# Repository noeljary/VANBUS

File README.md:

# VANBUS
Circuits and MCU Code for Camper Van Electronics Control Systems

VANBUS will be a series of circuit boards designed to control all electronic systems within a camper van conversion. It is based on a CANBUS network for inter-board communiciations.

This repository contains the Autodesk EAGLE files for the circuit boards, links to the custom designed cases, and the microcontroller code used to control the system.

Boards:
- LIGHTING_CTL_BOARD: Circuit Board for PWM Control of LED Lighting
- MOSFET_CTL_BOARD: Circuit Board for Fused Power Distribution with Voltage/Current per Channel Monitoring
- REMOTE_SWITCH_BOARD: Circuit Board for Remote Switching of MOSFET/Lighting Circuits with Momentary/Latched Switching, and Status Indication
- CAPACITIVE_SWITCH_BOARD: Circuit Board for Dimming Control of Lighting Circuits with Capacitive Touch Slider
- MOSFET_POC: Proof of Concept Circuit Board for MOSET based solid state relay system
- VANBUS_HUB: Circuit Board for Central Connection of CANBUS connectors where daisy chaining is not possible

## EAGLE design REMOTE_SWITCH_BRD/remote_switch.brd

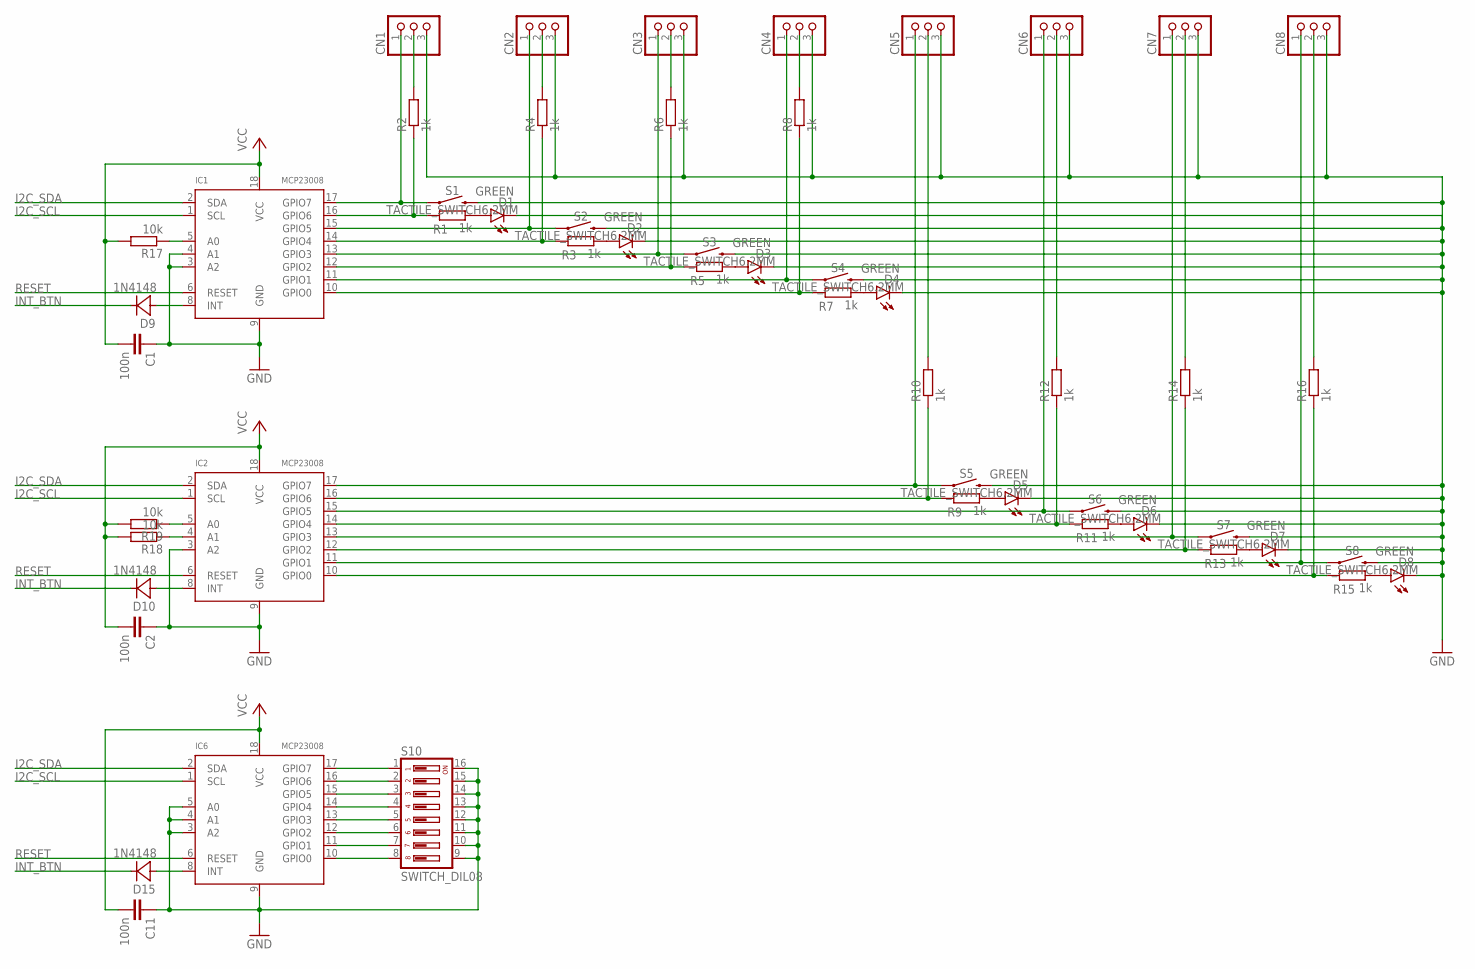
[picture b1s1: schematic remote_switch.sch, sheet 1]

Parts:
C1, C2, C11: 100n; C0805
CN1, CN2, CN3, CN4, CN5, CN6, CN7, CN8: JST_3PIN; JSTPH3
D1, D2, D3, D4, D5, D6, D7, D8: GREEN; CHIPLED_1206
D9, D10, D15: 1N4148; SOD123
IC1, IC2, IC6: MCP23008; SO18W
R1, R2, R3, R4, R5, R6, R7, R8, R9, R10, R11, R12, R13, R14, R15, R16: 1k; R0805
R17, R18, R19: 10k; R0805
S1, S2, S3, S4, S5, S6, S7, S8: TACTILE_SWITCH6.2MM; TACTILE_SWITCH_SMD_6.2MM
S10: SWITCH_DIL08; CTS-219-08

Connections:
GND: C1.1, C2.1, C11.1, CN1.3, CN2.3, CN3.3, CN4.3, CN5.3, CN6.3, CN7.3, CN8.3, D1.C, D2.C, D3.C, D4.C, D5.C, D6.C, D7.C, D8.C, IC1.3 (A2), IC1.4 (A1), IC1.9 (GND), IC2.3 (A2), IC2.9 (GND), IC6.3 (A2), IC6.4 (A1), IC6.5 (A0), IC6.9 (GND), S1.B1 (2), S1.B2 (2), S2.B1 (2), S2.B2 (2), S3.B1 (2), S3.B2 (2), S4.B1 (2), S4.B2 (2), S5.B1 (2), S5.B2 (2), S6.B1 (2), S6.B2 (2), S7.B1 (2), S7.B2 (2), S8.B1 (2), S8.B2 (2), S10.9, S10.10, S10.11, S10.12, S10.13, S10.14, S10.15, S10.16; also elsewhere on the board
I2C_SCL: IC1.1 (SCL), IC2.1 (SCL), IC6.1 (SCL); also elsewhere on the board
I2C_SDA: IC1.2 (SDA), IC2.2 (SDA), IC6.2 (SDA); also elsewhere on the board
INT_BTN: D9.C, D10.C, D15.C; also elsewhere on the board
unnamed: IC1.5 (A0), R17.1
unnamed: IC2.5 (A0), R19.1
unnamed: IC2.4 (A1), R18.1
unnamed: IC6.17 (GPIO7), S10.1
unnamed: IC6.16 (GPIO6), S10.2
unnamed: IC6.15 (GPIO5), S10.3
unnamed: IC6.14 (GPIO4), S10.4
unnamed: IC6.13 (GPIO3), S10.5
unnamed: IC6.12 (GPIO2), S10.6
unnamed: IC6.11 (GPIO1), S10.7
unnamed: CN1.1, IC1.17 (GPIO7), S1.A1 (1), S1.A2 (1)
unnamed: CN2.1, IC1.15 (GPIO5), S2.A1 (1), S2.A2 (1)
unnamed: CN3.1, IC1.13 (GPIO3), S3.A1 (1), S3.A2 (1)
unnamed: CN4.1, IC1.11 (GPIO1), S4.A1 (1), S4.A2 (1)
unnamed: CN5.1, IC2.17 (GPIO7), S5.A1 (1), S5.A2 (1)
unnamed: CN6.1, IC2.15 (GPIO5), S6.A1 (1), S6.A2 (1)
unnamed: CN7.1, IC2.13 (GPIO3), S7.A1 (1), S7.A2 (1)
unnamed: CN8.1, IC2.11 (GPIO1), S8.A1 (1), S8.A2 (1)
unnamed: D1.A, R1.2
unnamed: D2.A, R3.2
unnamed: D3.A, R5.2
unnamed: D4.A, R7.2
unnamed: D5.A, R9.2
unnamed: D6.A, R11.2
unnamed: D7.A, R13.2
unnamed: D8.A, R15.2
unnamed: CN1.2, R2.2
unnamed: IC1.16 (GPIO6), R1.1, R2.1
unnamed: CN2.2, R4.2
unnamed: CN3.2, R6.2
unnamed: CN4.2, R8.2
unnamed: CN5.2, R10.2
unnamed: CN6.2, R12.2
unnamed: CN7.2, R14.2
unnamed: CN8.2, R16.2
unnamed: IC1.14 (GPIO4), R3.1, R4.1
unnamed: IC1.12 (GPIO2), R5.1, R6.1
unnamed: IC1.10 (GPIO0), R7.1, R8.1
unnamed: IC2.16 (GPIO6), R9.1, R10.1
unnamed: IC2.14 (GPIO4), R11.1, R12.1
unnamed: IC2.12 (GPIO2), R13.1, R14.1
unnamed: IC2.10 (GPIO0), R15.1, R16.1
unnamed: IC6.10 (GPIO0), S10.8
unnamed: D10.A, IC2.8 (INT)
unnamed: D9.A, IC1.8 (INT)
unnamed: D15.A, IC6.8 (INT)
RESET: IC1.6 (RESET), IC2.6 (RESET), IC6.6 (RESET); also elsewhere on the board
VCC: C1.2, C2.2, C11.2, IC1.18 (VCC), IC2.18 (VCC), IC6.18 (VCC), R17.2, R18.2, R19.2; also elsewhere on the board

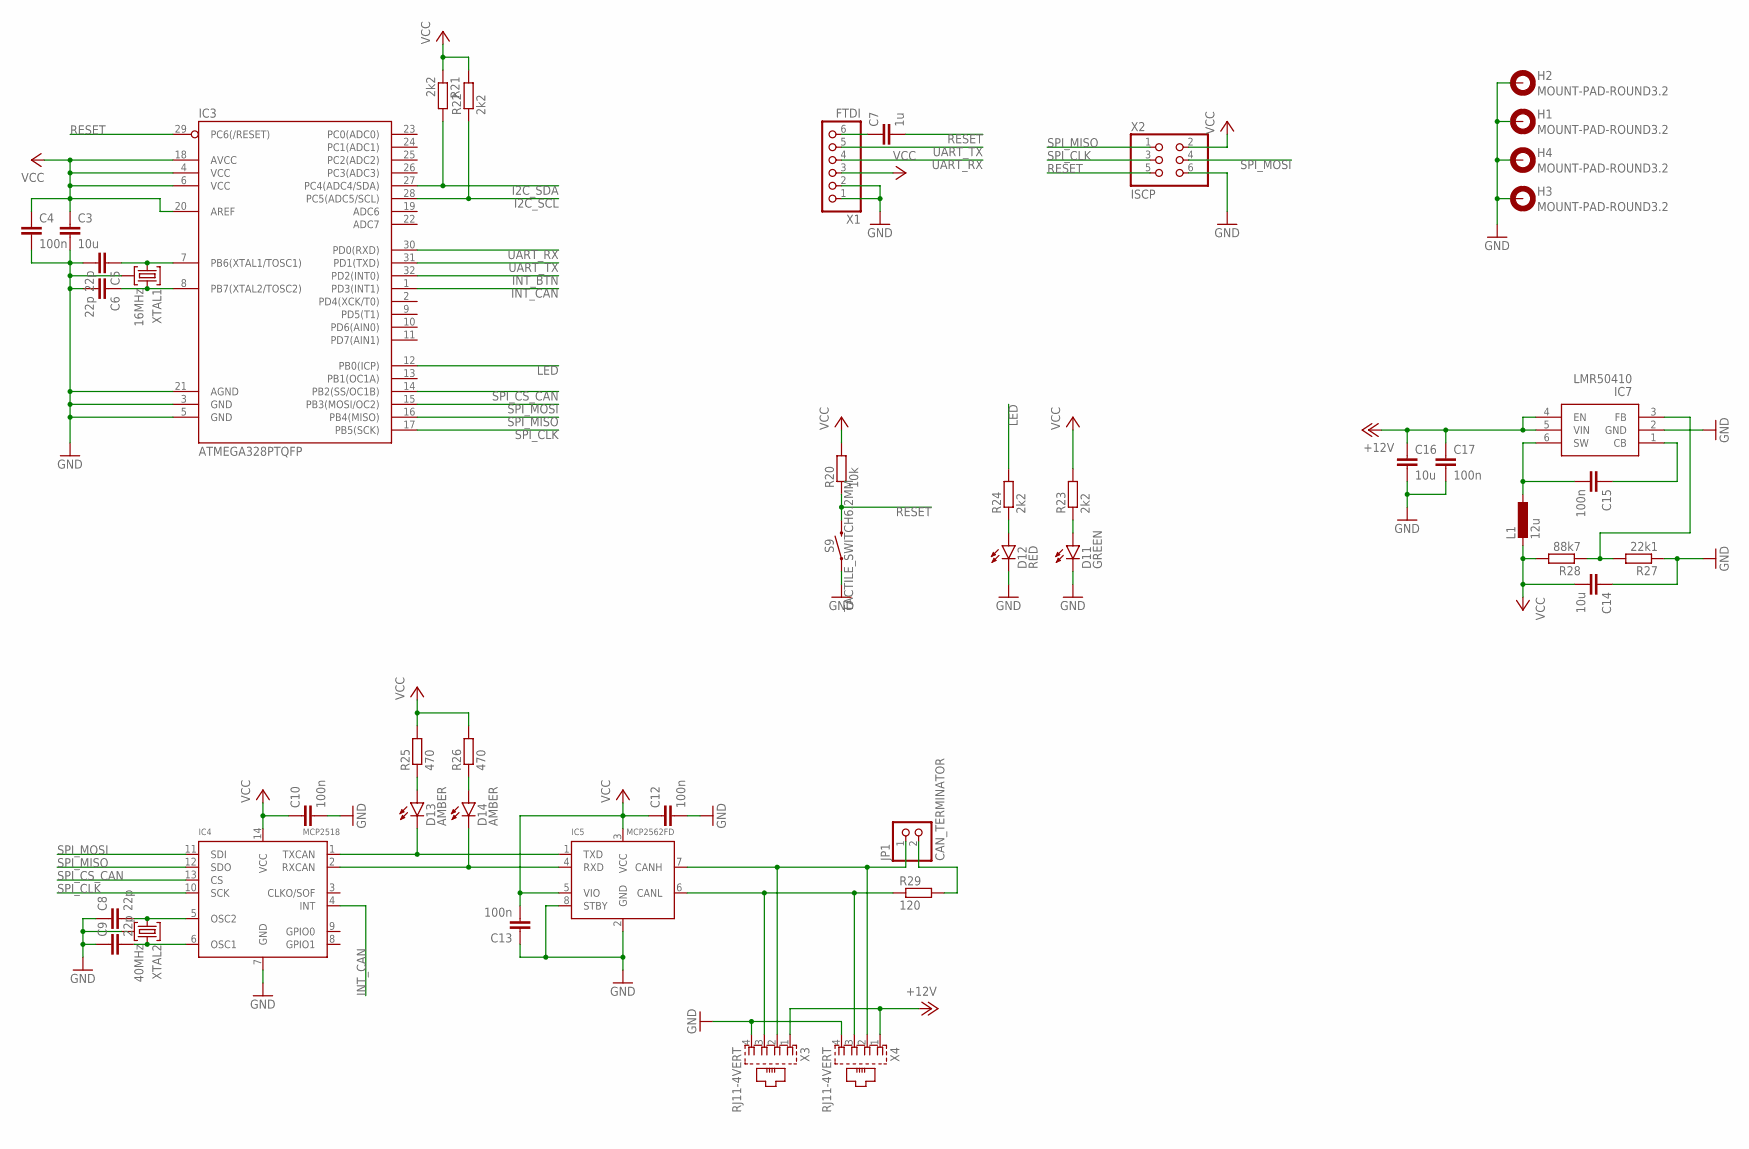
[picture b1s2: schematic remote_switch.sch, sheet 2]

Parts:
C3, C14, C16: 10u; C1206
C4, C10, C12, C13, C15, C17: 100n; C0805
C5, C6, C8, C9: 22p; C0805
C7: 1u; C0805
D11: GREEN; CHIPLED_1206
D12: RED; CHIPLED_1206
D13, D14: AMBER; CHIPLED_1206
H1, H2, H3, H4: MOUNT-PAD-ROUND3.2; 3,2-PAD
IC3: ATMEGA328PTQFP; TQFP32_0.8MM_7X7MM
IC4: MCP2518; SO14
IC5: MCP2562FD; SO08
IC7: LMR50410; SOT23-6
JP1: CAN_TERMINATOR; 1X02
L1: 12u; L_7.3MM
R20: 10k; R0805
R21, R22, R23, R24: 2k2; R0805
R25, R26: 470; R0805
R27: 22k1; R0805
R28: 88k7; R0805
R29: 120; R0805
S9: TACTILE_SWITCH6.2MM; TACTILE_SWITCH_SMD_6.2MM
X1: FTDI; 1X06
X2: ISCP; 2X03
X3, X4: RJ11-4VERT; RJ11-4_VERT
XTAL1: 16MHz; XTAL_5.0X3.2_4
XTAL2: 40MHz; XTAL_5.0X3.2_4

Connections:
+12V: C16.1, C17.1, IC7.4 (EN), IC7.5 (VIN), X3.1, X4.1
GND: C3.2, C4.2, C5.2, C6.2, C8.1, C9.1, C10.2, C12.2, C13.1, C14.1, C16.2, C17.2, D11.C, D12.C, H1.B3,2, H1.P$1, H1.P$2, H1.P$3, H1.P$4, H1.P$5, H1.P$6, H1.P$7, H1.P$8, H2.B3,2, H2.P$1, H2.P$2, H2.P$3, H2.P$4, H2.P$5, H2.P$6, H2.P$7, H2.P$8, H3.B3,2, H3.P$1, H3.P$2, H3.P$3, H3.P$4, H3.P$5, H3.P$6, H3.P$7, H3.P$8, H4.B3,2, H4.P$1, H4.P$2, H4.P$3, H4.P$4, H4.P$5, H4.P$6, H4.P$7, H4.P$8, IC3.3 (GND), IC3.5 (GND), IC3.21 (AGND), IC4.7 (GND), IC5.2 (GND), IC5.8 (STBY), IC7.2 (GND), R27.1, S9.A1 (1), S9.A2 (1), X1.1, X1.2, X2.6, X3.4, X4.4, XTAL1.2, XTAL1.4 (2), XTAL2.2, XTAL2.4 (2); also elsewhere on the board
I2C_SCL: IC3.28 (PC5(ADC5/SCL)), R22.1; also elsewhere on the board
I2C_SDA: IC3.27 (PC4(ADC4/SDA)), R21.2; also elsewhere on the board
INT_BTN: IC3.32 (PD2(INT0)); also elsewhere on the board
INT_CAN: IC3.1 (PD3(INT1)), IC4.4 (INT)
LED: IC3.12 (PB0(ICP)), R24.2
unnamed: D12.A, R24.1
unnamed: C5.1, IC3.7 (PB6(XTAL1/TOSC1)), XTAL1.1
unnamed: C6.1, IC3.8 (PB7(XTAL2/TOSC2)), XTAL1.3
unnamed: D11.A, R23.1
unnamed: C7.1, X1.6
unnamed: IC5.6 (CANL), R29.1, X3.3, X4.3
unnamed: IC5.7 (CANH), JP1.1, X3.2, X4.2
unnamed: D13.C, IC4.1 (TXCAN), IC5.1 (TXD)
unnamed: D14.C, IC4.2 (RXCAN), IC5.4 (RXD)
unnamed: C8.2, IC4.5 (OSC2), XTAL2.1
unnamed: C9.2, IC4.6 (OSC1), XTAL2.3
unnamed: D13.A, R25.1
unnamed: D14.A, R26.1
unnamed: JP1.2, R29.2
unnamed: C15.2, IC7.6 (SW), L1.1
unnamed: C15.1, IC7.1 (CB)
unnamed: IC7.3 (FB), R27.2, R28.1
RESET: C7.2, IC3.29 (PC6(/RESET)), R20.1, S9.B1 (2), S9.B2 (2), X2.5; also elsewhere on the board
SPI_CLK: IC3.17 (PB5(SCK)), IC4.10 (SCK), X2.3
SPI_CS_CAN: IC3.14 (PB2(SS/OC1B)), IC4.13 (CS)
SPI_MISO: IC3.16 (PB4(MISO)), IC4.12 (SDO), X2.1
SPI_MOSI: IC3.15 (PB3(MOSI/OC2)), IC4.11 (SDI), X2.4
UART_RX: IC3.30 (PD0(RXD)), X1.4
UART_TX: IC3.31 (PD1(TXD)), X1.5
VCC: C3.1, C4.1, C10.1, C12.1, C13.2, C14.2, IC3.4 (VCC), IC3.6 (VCC), IC3.18 (AVCC), IC3.20 (AREF), IC4.14 (VCC), IC5.3 (VCC), IC5.5 (VIO), L1.2, R20.2, R21.1, R22.2, R23.2, R25.2, R26.2, R28.2, X1.3, X2.2; also elsewhere on the board

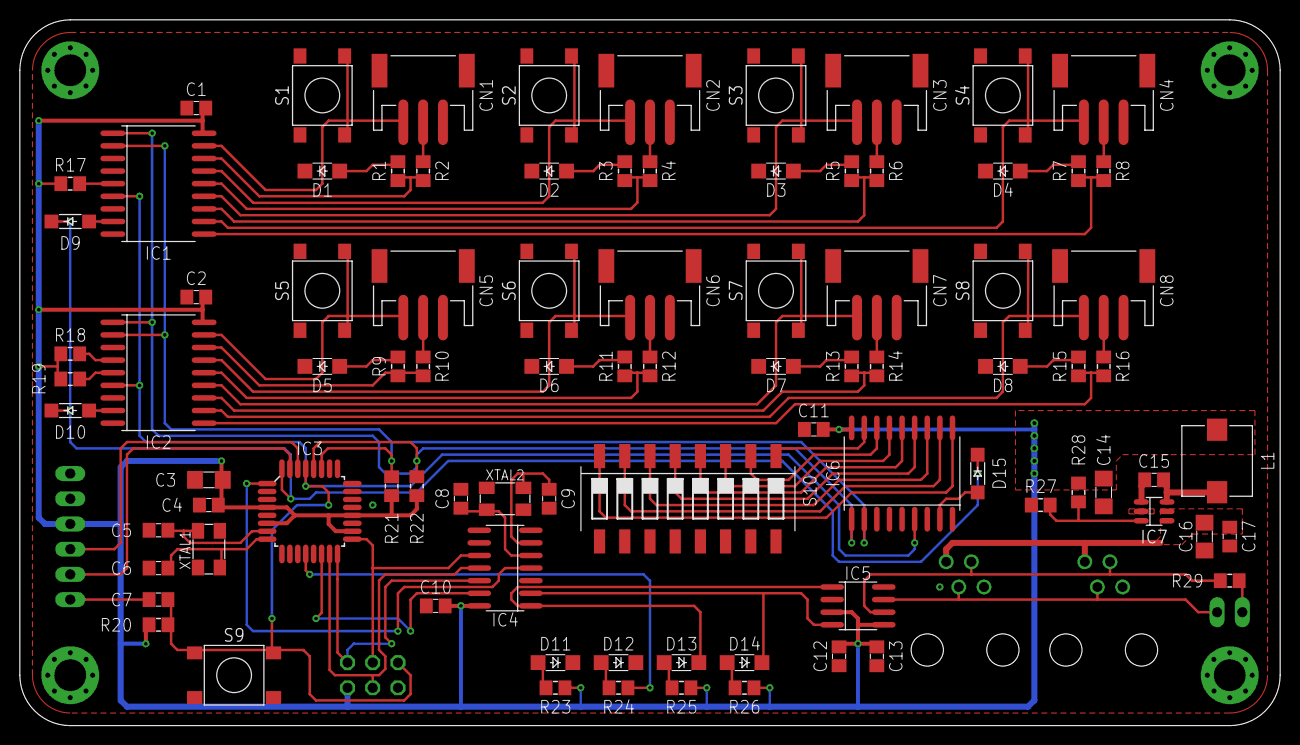
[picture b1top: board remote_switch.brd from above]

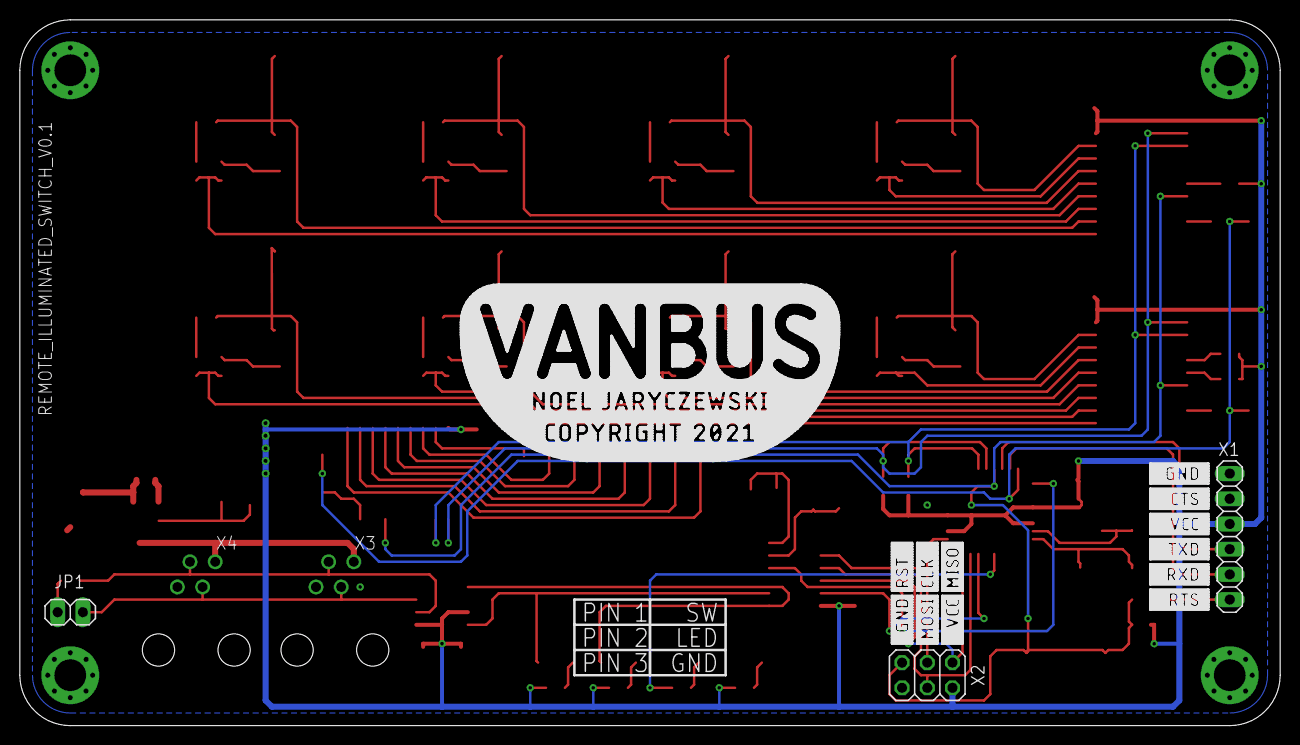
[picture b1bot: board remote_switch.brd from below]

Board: 2 copper layers, 127.0 x 71.1 mm, 98 parts (5 on the bottom side), 78 nets.

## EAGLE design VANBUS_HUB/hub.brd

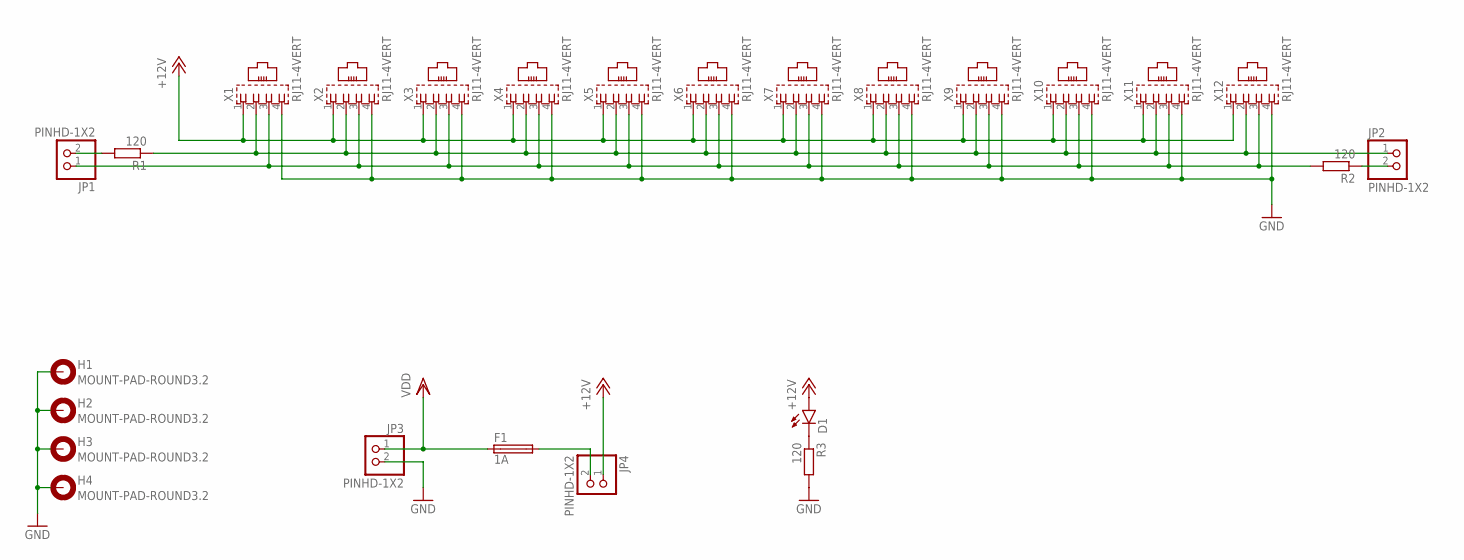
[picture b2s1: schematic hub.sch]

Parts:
D1: LED1206; CHIPLED_1206
F1: 1A; 5X20_FUSE
H1, H2, H3, H4: MOUNT-PAD-ROUND3.2; 3,2-PAD
JP1, JP2, JP3, JP4: PINHD-1X2; 1X02
R1, R2, R3: 120; R0805
X1, X2, X3, X4, X5, X6, X7, X8, X9, X10, X11, X12: RJ11-4VERT; RJ11-4_VERT

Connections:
+12V: D1.A, JP4.1, X1.1, X2.1, X3.1, X4.1, X5.1, X6.1, X7.1, X8.1, X9.1, X10.1, X11.1, X12.1
GND: H1.B3,2, H1.P$1, H1.P$2, H1.P$3, H1.P$4, H1.P$5, H1.P$6, H1.P$7, H1.P$8, H2.B3,2, H2.P$1, H2.P$2, H2.P$3, H2.P$4, H2.P$5, H2.P$6, H2.P$7, H2.P$8, H3.B3,2, H3.P$1, H3.P$2, H3.P$3, H3.P$4, H3.P$5, H3.P$6, H3.P$7, H3.P$8, H4.B3,2, H4.P$1, H4.P$2, H4.P$3, H4.P$4, H4.P$5, H4.P$6, H4.P$7, H4.P$8, JP3.2, R3.2, X1.4, X2.4, X3.4, X4.4, X5.4, X6.4, X7.4, X8.4, X9.4, X10.4, X11.4, X12.4
unnamed: JP2.2, R2.1
unnamed: JP2.1, R1.1, X1.2, X2.2, X3.2, X4.2, X5.2, X6.2, X7.2, X8.2, X9.2, X10.2, X11.2, X12.2
unnamed: JP1.1, R2.2, X1.3, X2.3, X3.3, X4.3, X5.3, X6.3, X7.3, X8.3, X9.3, X10.3, X11.3, X12.3
unnamed: JP1.2, R1.2
unnamed: D1.C, R3.1
unnamed: F1.2A (2), F1.2B (2), JP4.2
VDD: F1.1A (1), F1.1B (1), JP3.1

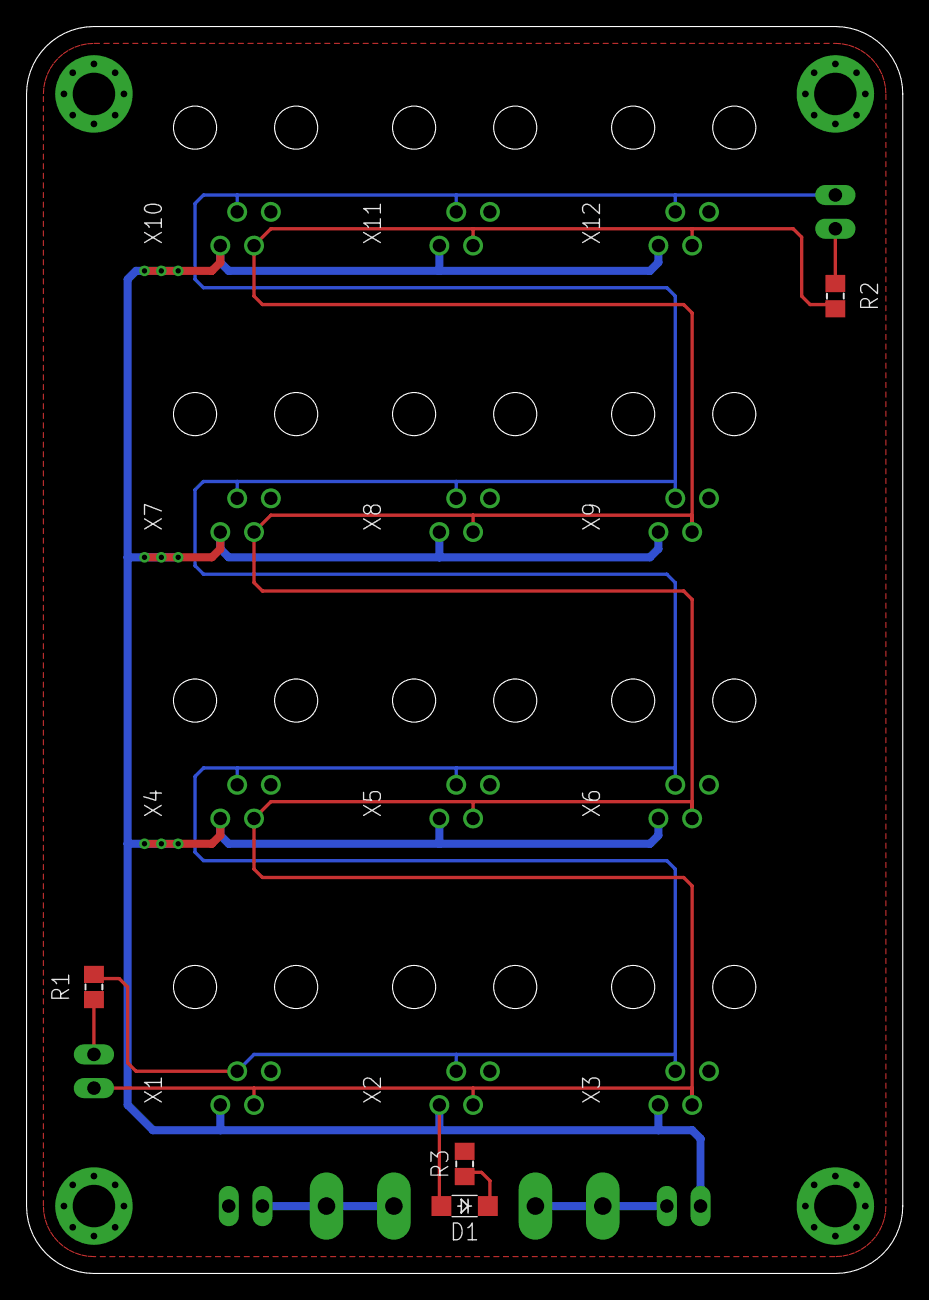
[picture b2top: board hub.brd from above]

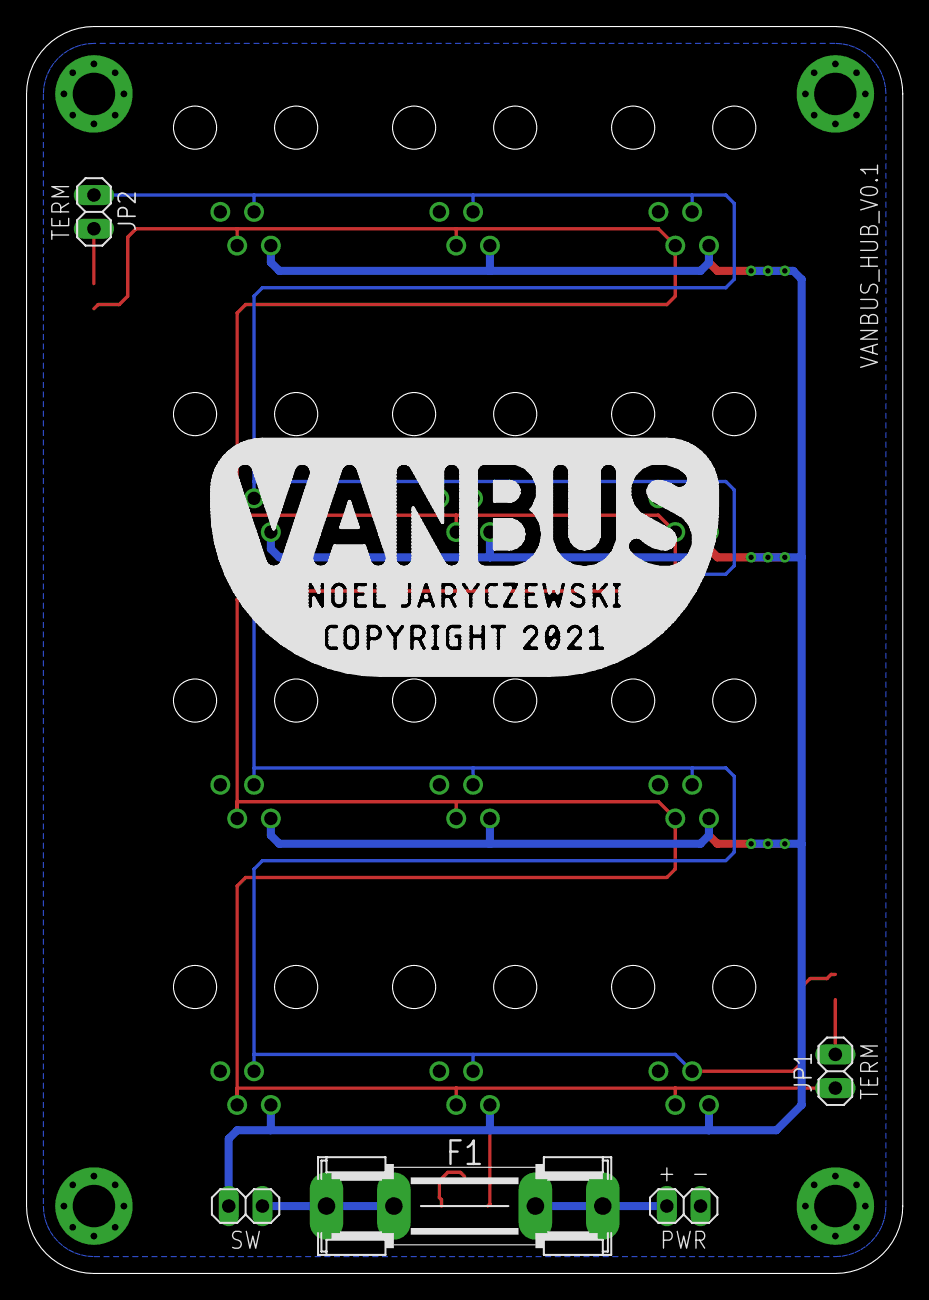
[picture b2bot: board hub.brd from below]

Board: 2 copper layers, 66.0 x 94.0 mm, 25 parts (5 on the bottom side), 9 nets.

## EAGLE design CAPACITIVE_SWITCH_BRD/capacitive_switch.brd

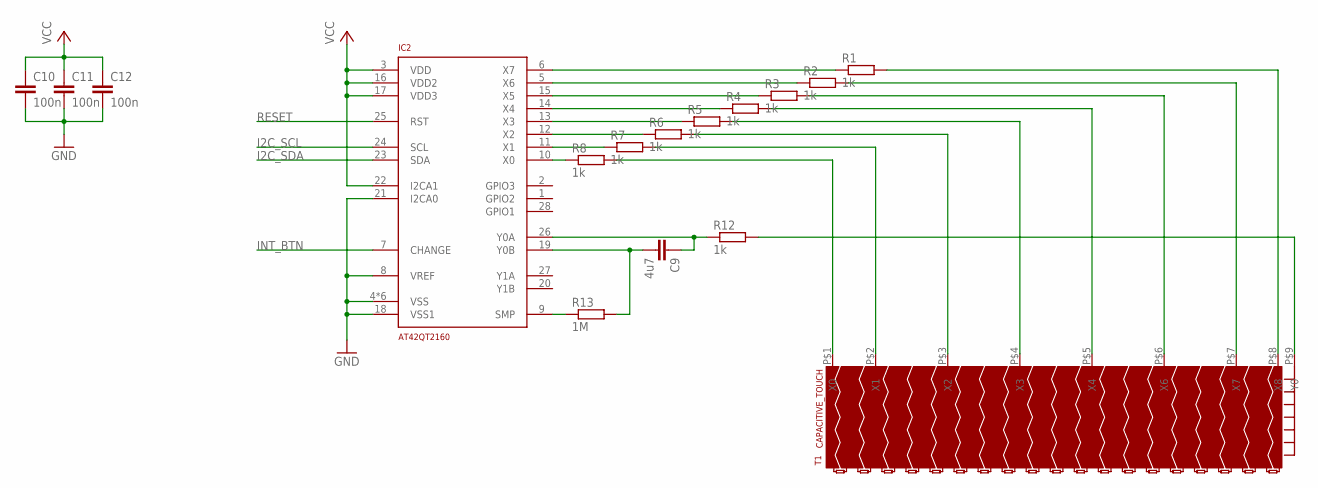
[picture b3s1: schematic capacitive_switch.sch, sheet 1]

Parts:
C9: 4u7; C0805
C10, C11, C12: 100n; C0805
IC2: AT42QT2160; QFN28_0.45MM_4X4MM
R1, R2, R3, R4, R5, R6, R7, R8, R12: 1k; R0805
R13: 1M; R0805
T1: CAPACITIVE_TOUCH; 90X20_CAPACITIVE_TOUCH

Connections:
GND: C10.2, C11.2, C12.2, IC2.4 (VSS), IC2.8 (VREF), IC2.18 (VSS1), IC2.21 (I2CA0), IC2.29 (VSS), IC2.P$1 (VSS), IC2.P$2 (VSS), IC2.P$3 (VSS), IC2.P$4 (VSS); also elsewhere on the board
I2C_SCL: IC2.24 (SCL); also elsewhere on the board
I2C_SDA: IC2.23 (SDA); also elsewhere on the board
INT_BTN: IC2.7 (CHANGE); also elsewhere on the board
unnamed: R8.2, T1.P$1 (X0)
unnamed: R7.2, T1.P$2 (X1)
unnamed: R6.2, T1.P$3 (X2)
unnamed: R5.2, T1.P$4 (X3)
unnamed: R4.2, T1.P$5 (X4)
unnamed: R3.2, T1.P$6 (X6)
unnamed: R2.2, T1.P$7 (X7)
unnamed: R1.2, T1.P$8 (X8)
unnamed: R12.2, T1.P$9 (Y0)
unnamed: C9.1, IC2.26 (Y0A), R12.1
unnamed: IC2.10 (X0), R8.1
unnamed: IC2.11 (X1), R7.1
unnamed: IC2.12 (X2), R6.1
unnamed: IC2.13 (X3), R5.1
unnamed: IC2.14 (X4), R4.1
unnamed: IC2.15 (X5), R3.1
unnamed: IC2.5 (X6), R2.1
unnamed: IC2.6 (X7), R1.1
unnamed: C9.2, IC2.19 (Y0B), R13.2
unnamed: IC2.9 (SMP), R13.1
RESET: IC2.25 (RST); also elsewhere on the board
VCC: C10.1, C11.1, C12.1, IC2.3 (VDD), IC2.16 (VDD2), IC2.17 (VDD3), IC2.22 (I2CA1); also elsewhere on the board

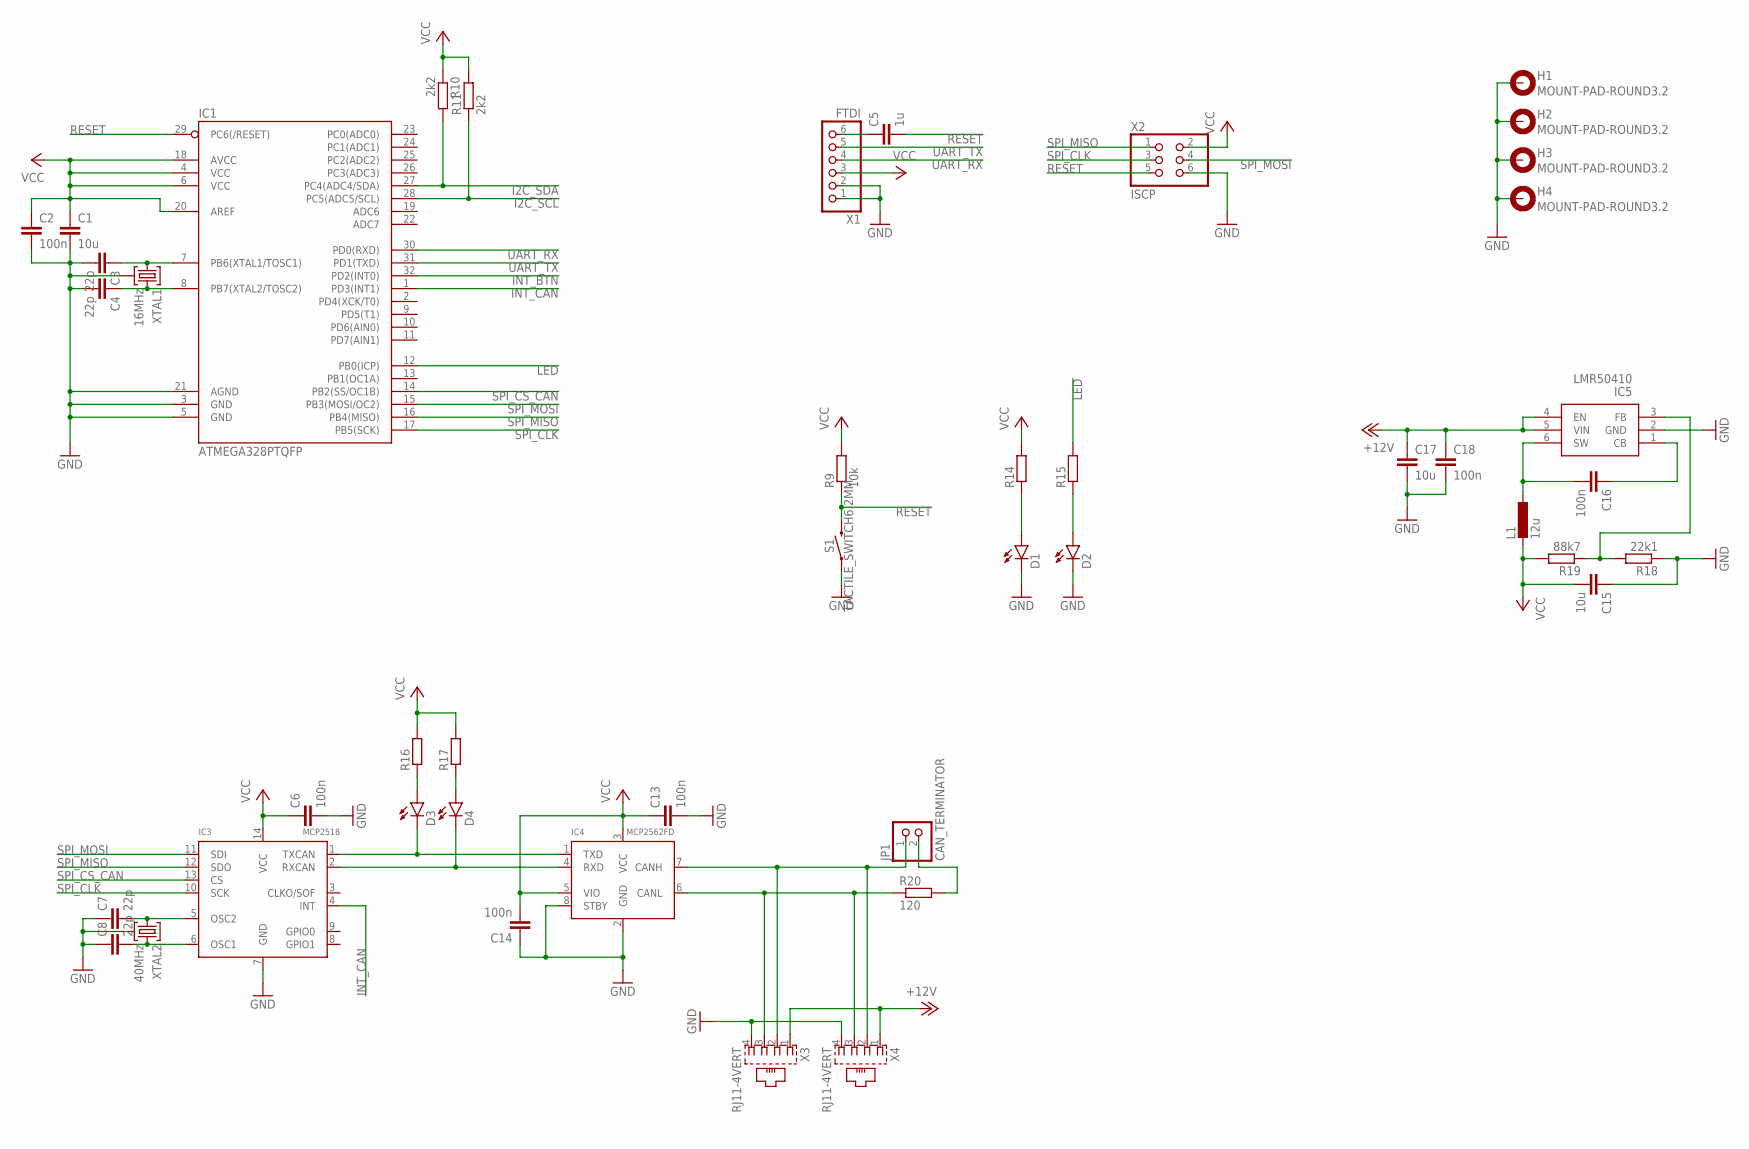
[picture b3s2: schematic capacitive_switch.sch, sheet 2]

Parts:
C1, C15, C17: 10u; C1206
C2, C6, C13, C14, C16, C18: 100n; C0805
C3, C4, C7, C8: 22p; C0805
C5: 1u; C0805
D1, D2, D3, D4: LED1206; CHIPLED_1206
H1, H2, H3, H4: MOUNT-PAD-ROUND3.2; 3,2-PAD
IC1: ATMEGA328PTQFP; TQFP32_0.8MM_7X7MM
IC3: MCP2518; SO14
IC4: MCP2562FD; SO08
IC5: LMR50410; SOT23-6
JP1: CAN_TERMINATOR; 1X02
L1: 12u; L_7.3MM
R9: 10k; R0805
R10, R11: 2k2; R0805
R14, R15, R16, R17: RESISTOR0805; R0805
R18: 22k1; R0805
R19: 88k7; R0805
R20: 120; R0805
S1: TACTILE_SWITCH6.2MM; TACTILE_SWITCH_SMD_6.2MM
X1: FTDI; 1X06
X2: ISCP; 2X03
X3, X4: RJ11-4VERT; RJ11-4_VERT
XTAL1: 16MHz; XTAL_5.0X3.2_4
XTAL2: 40MHz; XTAL_5.0X3.2_4

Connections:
+12V: C17.1, C18.1, IC5.4 (EN), IC5.5 (VIN), X3.1, X4.1
GND: C1.2, C2.2, C3.2, C4.2, C6.2, C7.1, C8.1, C13.2, C14.1, C15.1, C17.2, C18.2, D1.C, D2.C, H1.B3,2, H1.P$1, H1.P$2, H1.P$3, H1.P$4, H1.P$5, H1.P$6, H1.P$7, H1.P$8, H2.B3,2, H2.P$1, H2.P$2, H2.P$3, H2.P$4, H2.P$5, H2.P$6, H2.P$7, H2.P$8, H3.B3,2, H3.P$1, H3.P$2, H3.P$3, H3.P$4, H3.P$5, H3.P$6, H3.P$7, H3.P$8, H4.B3,2, H4.P$1, H4.P$2, H4.P$3, H4.P$4, H4.P$5, H4.P$6, H4.P$7, H4.P$8, IC1.3 (GND), IC1.5 (GND), IC1.21 (AGND), IC3.7 (GND), IC4.2 (GND), IC4.8 (STBY), IC5.2 (GND), R18.1, S1.A1 (1), S1.A2 (1), X1.1, X1.2, X2.6, X3.4, X4.4, XTAL1.2, XTAL1.4 (2), XTAL2.2, XTAL2.4 (2); also elsewhere on the board
I2C_SCL: IC1.28 (PC5(ADC5/SCL)), R11.1; also elsewhere on the board
I2C_SDA: IC1.27 (PC4(ADC4/SDA)), R10.2; also elsewhere on the board
INT_BTN: IC1.32 (PD2(INT0)); also elsewhere on the board
INT_CAN: IC1.1 (PD3(INT1)), IC3.4 (INT)
LED: IC1.12 (PB0(ICP)), R15.2
unnamed: D3.A, R16.1
unnamed: C3.1, IC1.7 (PB6(XTAL1/TOSC1)), XTAL1.1
unnamed: C4.1, IC1.8 (PB7(XTAL2/TOSC2)), XTAL1.3
unnamed: D4.A, R17.1
unnamed: C5.1, X1.6
unnamed: IC4.6 (CANL), R20.1, X3.3, X4.3
unnamed: IC4.7 (CANH), JP1.1, X3.2, X4.2
unnamed: D3.C, IC3.1 (TXCAN), IC4.1 (TXD)
unnamed: D4.C, IC3.2 (RXCAN), IC4.4 (RXD)
unnamed: C7.2, IC3.5 (OSC2), XTAL2.1
unnamed: C8.2, IC3.6 (OSC1), XTAL2.3
unnamed: D1.A, R14.1
unnamed: D2.A, R15.1
unnamed: JP1.2, R20.2
unnamed: C16.2, IC5.6 (SW), L1.1
unnamed: C16.1, IC5.1 (CB)
unnamed: IC5.3 (FB), R18.2, R19.1
RESET: C5.2, IC1.29 (PC6(/RESET)), R9.1, S1.B1 (2), S1.B2 (2), X2.5; also elsewhere on the board
SPI_CLK: IC1.17 (PB5(SCK)), IC3.10 (SCK), X2.3
SPI_CS_CAN: IC1.14 (PB2(SS/OC1B)), IC3.13 (CS)
SPI_MISO: IC1.16 (PB4(MISO)), IC3.12 (SDO), X2.1
SPI_MOSI: IC1.15 (PB3(MOSI/OC2)), IC3.11 (SDI), X2.4
UART_RX: IC1.30 (PD0(RXD)), X1.4
UART_TX: IC1.31 (PD1(TXD)), X1.5
VCC: C1.1, C2.1, C6.1, C13.1, C14.2, C15.2, IC1.4 (VCC), IC1.6 (VCC), IC1.18 (AVCC), IC1.20 (AREF), IC3.14 (VCC), IC4.3 (VCC), IC4.5 (VIO), L1.2, R9.2, R10.1, R11.2, R14.2, R16.2, R17.2, R19.2, X1.3, X2.2; also elsewhere on the board

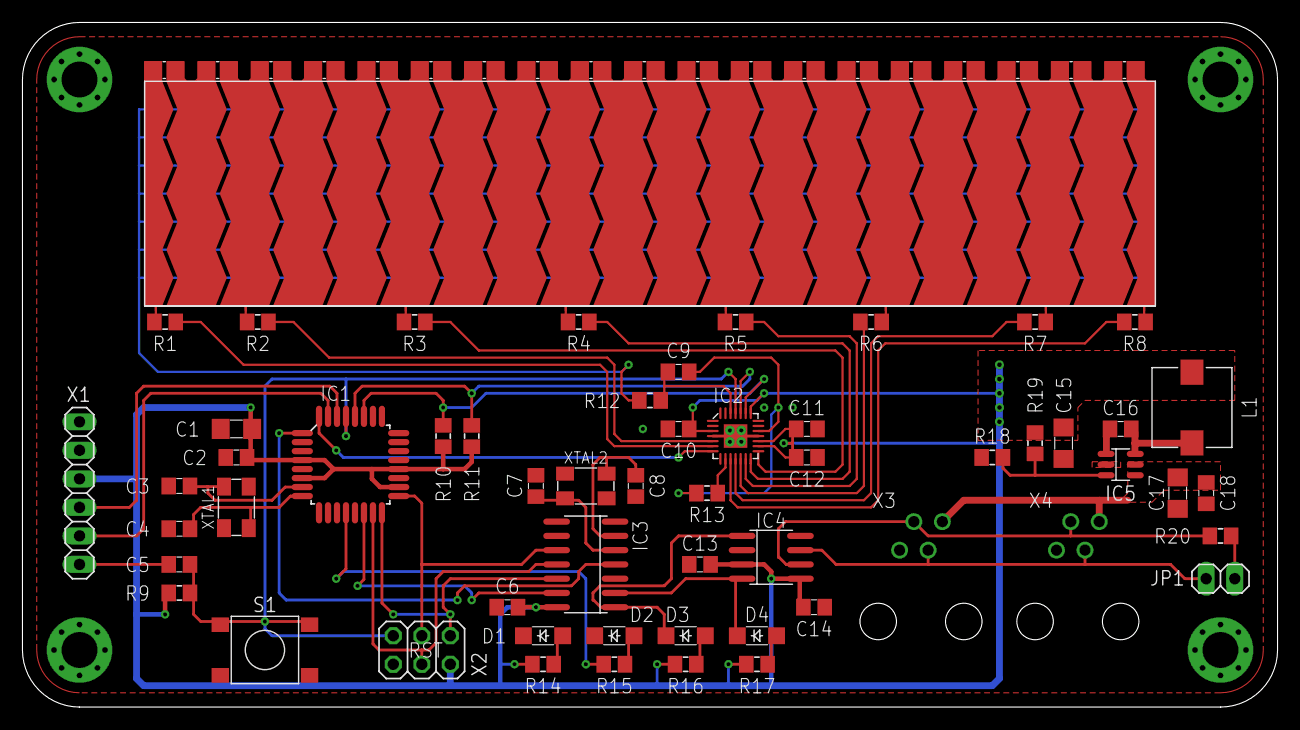
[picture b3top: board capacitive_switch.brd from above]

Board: 2 copper layers, 111.8 x 61.0 mm, 61 parts (0 on the bottom side), 52 nets.
